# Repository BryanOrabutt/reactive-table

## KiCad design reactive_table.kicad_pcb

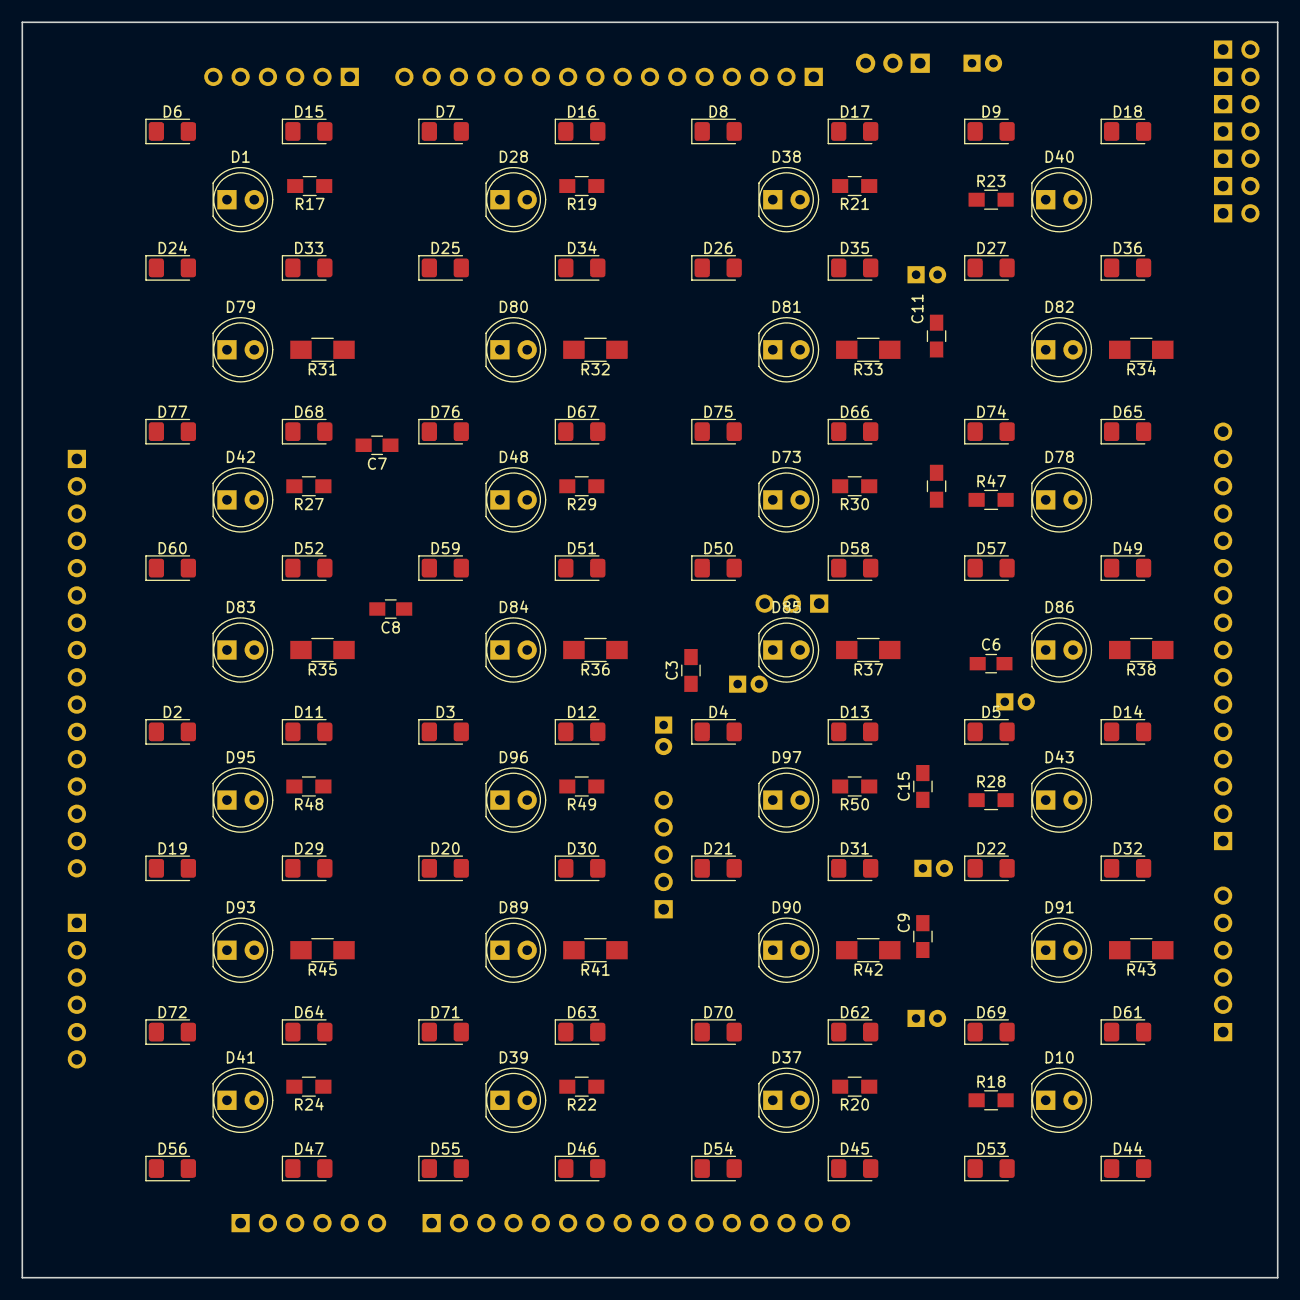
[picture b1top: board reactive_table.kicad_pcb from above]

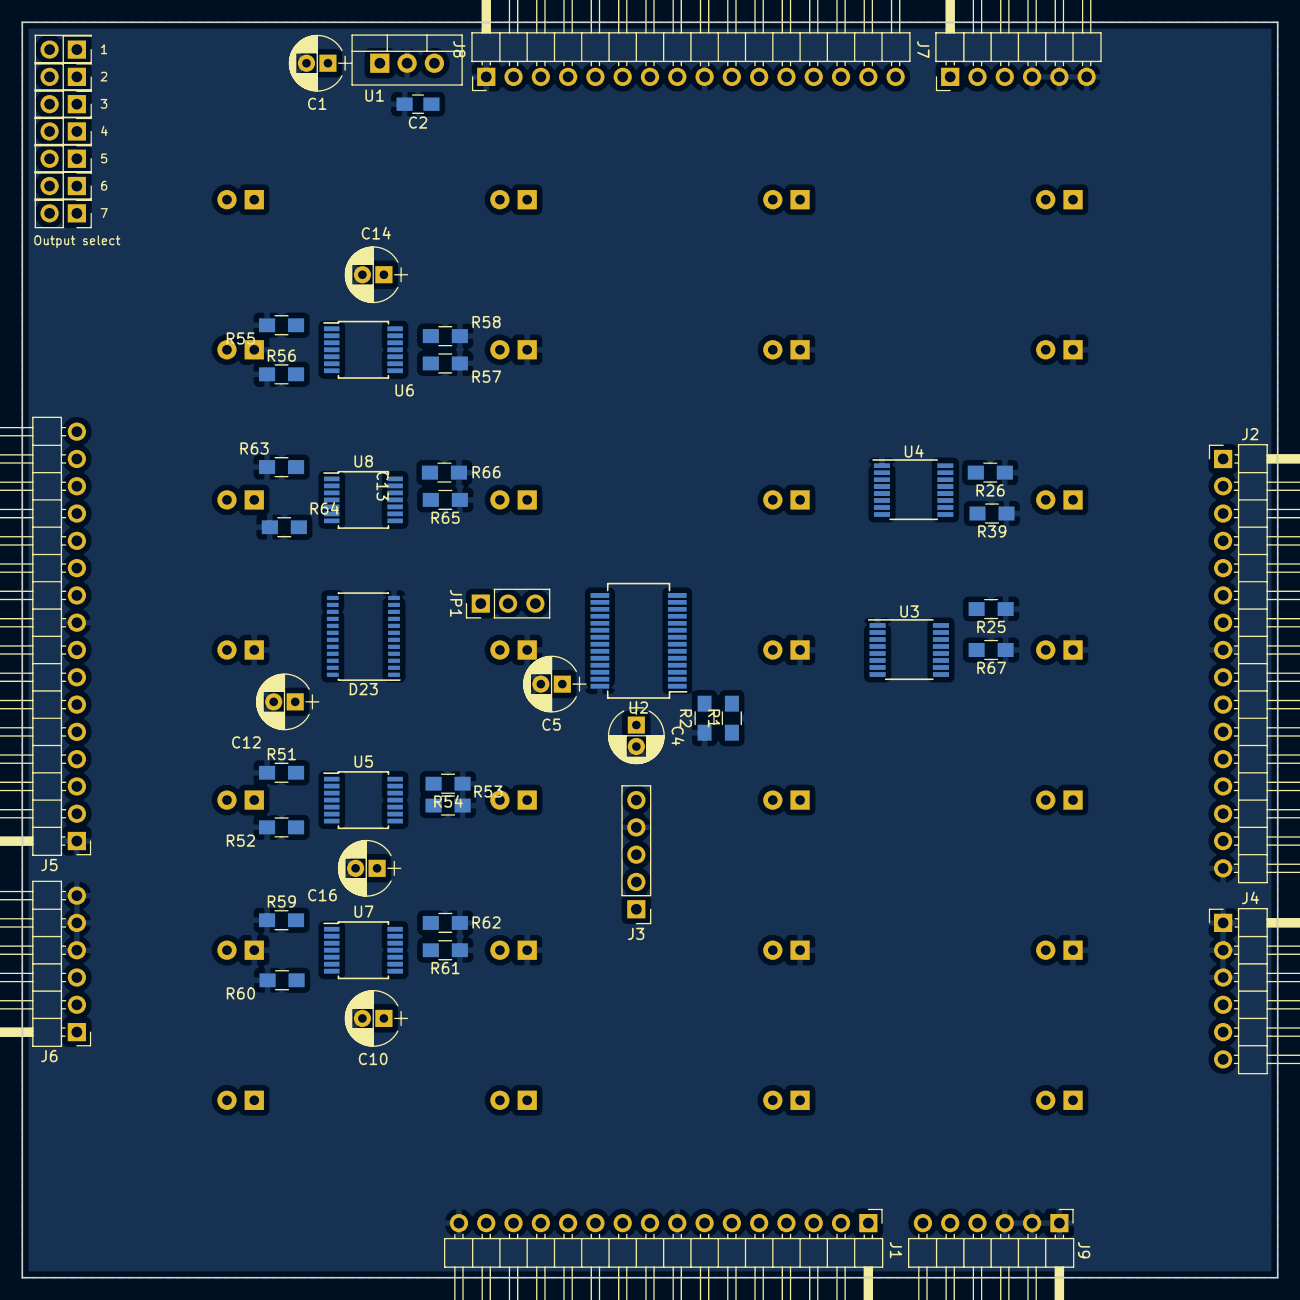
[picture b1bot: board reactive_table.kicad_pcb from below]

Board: 4 copper layers, 116.8 x 116.8 mm, 184 parts (56 on the bottom side), 137 nets, no tracks yet.

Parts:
C1, C4, C5, C10, C12, C14, C16: 1u; CP_Radial_D5.0mm_P2.00mm
C2, C3, C6, C7, C8, C9, C11, C13, C15: 100n; C_0805_HandSoldering
D1, D10, D28, D37, D38, D39, D40, D41, D42, D43, D48, D73, D78, D95, D96, D97: IR_RX; LED_D5.0mm
D2, D3, D4, D5, D6, D7, D8, D9, D11, D12, D13, D14, D15, D16, D17, D18, D19, D20, D21, D22, D24, D25, D26, D27, D29, D30, D31, D32, D33, D34, D35, D36, D44, D45, D46, D47, D49, D50, D51, D52, D53, D54, D55, D56, D57, D58, D59, D60, D61, D62, D63, D64, D65, D66, D67, D68, D69, D70, D71, D72, D74, D75, D76, D77: LED_Small; LED_1206_3216Metric_Pad1.42x1.75mm_HandSolder
D23: 74HC4067; TSSOP-24_4.4x7.8mm_Pitch0.65mm
D79, D80, D81, D82, D83, D84, D85, D86, D89, D90, D91, D93: IR_TX; LED_D5.0mm
J1: BOT; Pin_Header_Angled_1x16_Pitch2.54mm
J2: LEFT; Pin_Header_Angled_1x16_Pitch2.54mm
J3: PROGRAM; Pin_Header_Straight_1x05_Pitch2.54mm
J4: PWR_LEFT; Pin_Header_Angled_1x06_Pitch2.54mm
J5: RIGHT; Pin_Header_Angled_1x16_Pitch2.54mm
J6: PWR_RIGHT; Pin_Header_Angled_1x06_Pitch2.54mm
J7: PWR_BOT; Pin_Header_Angled_1x06_Pitch2.54mm
J8: TOP; Pin_Header_Angled_1x16_Pitch2.54mm
J9: PWR_TOP; Pin_Header_Angled_1x06_Pitch2.54mm
JP1: MASTER_SEL; Pin_Header_Straight_1x03_Pitch2.54mm
JP2, JP3, JP4, JP5, JP6, JP7, JP8: Jumper_NO_Small; Pin_Header_Straight_2x01_Pitch2.54mm
R1, R17, R18, R19, R20, R21, R22, R23, R24, R27, R28, R29, R30, R47, R48, R49, R50: 1K5; R_0805_HandSoldering
R2, R25, R26, R39, R67: 2K2; R_0805_HandSoldering
R31, R32, R33, R34, R35, R36, R37, R38, R41, R42, R43, R45: 300; R_1206_HandSoldering
R51, R52, R53, R54, R55, R56, R57, R58, R59, R60, R61, R62, R63, R64, R65, R66: 1M; R_0805_HandSoldering
U1: uA7805; TO-220-3_Vertical
U2: CY8C4124PVI-432; SSOP-28_5.3x10.2mm_Pitch0.65mm
U3, U4: STP08DP05; TSSOP-16_4.4x5mm_Pitch0.65mm
U5, U6, U7, U8: TLC274; TSSOP-14_4.4x5mm_Pitch0.65mm

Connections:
+5V: C2.1, C3.2, C4.1, C6.1, C7.2, C8.2, C9.1, C10.1, C11.1, C12.1, C13.1, C14.1, C15.1, C16.1, D1.1, D10.1, D23.24, D37.1, D39.1, D41.1, D43.1, J3.5, U1.3, U2.27, U3.16, U4.16, U5.4, U6.4, U7.4, U8.4
+12V: C1.1, D2.2, D3.2, D4.2, D5.2, D6.2, D7.2, D8.2, D9.2, D28.1, D38.1, D40.1, D42.1, D48.1, D69.2, D70.2, D71.2, D72.2, D73.1, D74.2, D75.2, D76.2, D77.2, D78.1, D95.1, D96.1, D97.1, J4.4, J4.5, J4.6, J6.1, J6.2, J6.3, J7.1, J7.2, J7.3, J9.4, J9.5, J9.6, R31.1, R32.1, R33.1, R34.1, R35.1, R36.1, R37.1, R38.1, R41.1, R42.1, R43.1, R45.1, U1.1
/BRD1: J1.7, J2.7, J5.10, J8.10, JP8.2, U2.4
/BRD2: J1.6, J2.6, J5.11, J8.11, JP7.2, U2.5
/BRD3: J1.5, J2.5, J5.12, J8.12, JP6.2, U2.6
/BRD4: J1.4, J2.4, J5.13, J8.13, JP5.2, U2.7
/BRD5: J1.3, J2.3, J5.14, J8.14, JP4.2, U2.8
/BRD6: J1.2, J2.2, J5.15, J8.15, JP3.2, U2.9
/BRD7: J1.1, J2.1, J5.16, J8.16, JP2.2, U2.10
/CLK: J1.14, J2.14, J5.3, J8.3, U2.20, U3.3, U4.3
/LE: J1.13, J2.13, J5.4, J8.4, U2.21, U3.4, U4.4
/LED Drivers & MUXs/DRIVER_SDI: JP1.2, U4.2
/LED Drivers & MUXs/DRIVER_SDO: J5.2, J8.2, U3.14
/LED Drivers & MUXs/IR0: D1.2, R17.2, R51.2, U5.3
/LED Drivers & MUXs/IR1: D28.2, R19.2, R52.2, U5.5
/LED Drivers & MUXs/IR2: D38.2, R21.2, R53.2, U5.10
/LED Drivers & MUXs/IR3: D40.2, R23.2, R54.2, U5.12
/LED Drivers & MUXs/IR4: D42.2, R27.2, R55.2, U6.3
/LED Drivers & MUXs/IR5: D48.2, R29.2, R56.2, U6.5
/LED Drivers & MUXs/IR6: D73.2, R30.2, R57.2, U6.10
/LED Drivers & MUXs/IR7: D78.2, R47.2, R58.2, U6.12
/LED Drivers & MUXs/IR8: D95.2, R48.2, R59.2, U7.3
/LED Drivers & MUXs/IR9: D96.2, R49.2, R60.2, U7.5
/LED Drivers & MUXs/IR10: D97.2, R50.2, R61.2, U7.10
/LED Drivers & MUXs/IR11: D43.2, R28.2, R62.2, U7.12
/LED Drivers & MUXs/IR12: D41.2, R24.2, R63.2, U8.3
/LED Drivers & MUXs/IR13: D39.2, R22.2, R64.2, U8.5
/LED Drivers & MUXs/IR14: D37.2, R20.2, R65.2, U8.10
/LED Drivers & MUXs/IR15: D10.2, R18.2, R66.2, U8.12
/LED Drivers & MUXs/sdo: U3.2, U4.14
/MUX0: D23.10, J1.9, J2.9, J5.8, J8.8, U2.18
/MUX1: D23.11, J1.10, J2.10, J5.7, J8.7, U2.17
/MUX2: D23.14, J1.11, J2.11, J5.6, J8.6, U2.16
/MUX3: D23.13, J1.12, J2.12, J5.5, J8.5, U2.15
/MUX_IN0: D23.9, U5.1, U5.2
/MUX_IN1: D23.8, U5.6, U5.7
/MUX_IN2: D23.7, U5.8, U5.9
/MUX_IN3: D23.6, U5.13, U5.14
/MUX_IN4: D23.5, U6.1, U6.2
/MUX_IN5: D23.4, U6.6, U6.7
/MUX_IN6: D23.3, U6.8, U6.9
/MUX_IN7: D23.2, U6.13, U6.14
/MUX_IN8: D23.23, U7.1, U7.2
/MUX_IN9: D23.22, U7.6, U7.7
/MUX_IN10: D23.21, U7.8, U7.9
/MUX_IN11: D23.20, U7.13, U7.14
/MUX_IN12: D23.19, U8.1, U8.2
/MUX_IN13: D23.18, U8.6, U8.7
/MUX_IN14: D23.17, U8.8, U8.9
/MUX_IN15: D23.16, U8.13, U8.14
/Microcontroller/BOARD0: JP2.1, JP3.1, JP4.1, JP5.1, JP6.1, JP7.1, JP8.1, R1.2, R2.1, U2.3
/Microcontroller/PSOC_SDO: JP1.1, U2.19
/Microcontroller/RST: J3.3, U2.25
/Microcontroller/SWDCLK: J3.2, U2.14
/Microcontroller/SWDIO: J3.1, U2.13
/SDI: J1.15, J2.15, JP1.3
GND: C1.2, C2.2, C3.1, C4.2, C5.2, C6.2, C7.1, C8.1, C9.2, C10.2, C11.2, C12.2, C13.2, C14.2, C15.2, C16.2, D23.12, D23.15, D79.1, D80.1, D81.1, D82.1, D83.1, D84.1, D85.1, D86.1, D89.1, D90.1, D91.1, D93.1, J1.8, J1.16, J2.8, J2.16, J3.4, J4.1, J4.2, J4.3, J5.1, J5.9, J6.4, J6.5, J6.6, J7.4, J7.5, J7.6, J8.1, J8.9, J9.1, J9.2, J9.3, R2.2, R17.1, R18.1, R19.1, R20.1, R21.1, R22.1, R23.1, R24.1, R25.1, R26.1, R27.1, R28.1, R29.1, R30.1, R39.1, R47.1, R48.1, R49.1, R50.1, R51.1, R52.1, R53.1, R54.1, R55.1, R56.1, R57.1, R58.1, R59.1, R60.1, R61.1, R62.1, R63.1, R64.1, R65.1, R66.1, R67.1, U1.2, U2.28, U3.1, U4.1, U5.11, U6.11, U7.11, U8.11
unnamed: C5.1, U2.26
unnamed: D11.1, D19.2
unnamed: D2.1, D11.2
unnamed: D12.1, D20.2
unnamed: D3.1, D12.2
unnamed: D13.1, D21.2
unnamed: D4.1, D13.2
unnamed: D14.1, D22.2
unnamed: D5.1, D14.2
unnamed: D15.1, D24.2
unnamed: D6.1, D15.2
unnamed: D16.1, D25.2
unnamed: D7.1, D16.2
unnamed: D17.1, D26.2
unnamed: D8.1, D17.2
unnamed: D18.1, D27.2
unnamed: D9.1, D18.2
unnamed: D19.1, D29.2
unnamed: D20.1, D30.2
unnamed: D21.1, D31.2
unnamed: D22.1, D32.2
unnamed: D23.1, R1.1
unnamed: D24.1, D33.2
unnamed: D25.1, D34.2
unnamed: D26.1, D35.2
unnamed: D27.1, D36.2
unnamed: D29.1, U3.5
unnamed: D30.1, U3.6
unnamed: D31.1, U3.7
unnamed: D32.1, U3.8
unnamed: D33.1, U4.5
unnamed: D34.1, U4.6
unnamed: D35.1, U4.7
unnamed: D36.1, U4.8
unnamed: D44.1, U3.12
unnamed: D44.2, D53.1
unnamed: D45.1, U3.11
unnamed: D45.2, D54.1
unnamed: D46.1, U3.10
unnamed: D46.2, D55.1
unnamed: D47.1, U3.9
unnamed: D47.2, D56.1
unnamed: D49.1, U4.12
unnamed: D49.2, D57.1
unnamed: D50.1, U4.11
unnamed: D50.2, D58.1
unnamed: D51.1, U4.10
unnamed: D51.2, D59.1
unnamed: D52.1, U4.9
unnamed: D52.2, D60.1
unnamed: D53.2, D61.1
unnamed: D54.2, D62.1
unnamed: D55.2, D63.1
unnamed: D56.2, D64.1
unnamed: D57.2, D65.1
unnamed: D58.2, D66.1
unnamed: D59.2, D67.1
unnamed: D60.2, D68.1
unnamed: D61.2, D69.1
unnamed: D62.2, D70.1
unnamed: D63.2, D71.1
unnamed: D64.2, D72.1
unnamed: D65.2, D74.1
unnamed: D66.2, D75.1
unnamed: D67.2, D76.1
unnamed: D68.2, D77.1
unnamed: D79.2, R31.2
unnamed: D80.2, R32.2
unnamed: D81.2, R33.2
unnamed: D82.2, R34.2
unnamed: D83.2, R35.2
unnamed: D84.2, R36.2
unnamed: D85.2, R37.2
unnamed: D86.2, R38.2
unnamed: D89.2, R41.2
unnamed: D90.2, R42.2
unnamed: D91.2, R43.2
unnamed: D93.2, R45.2
unnamed: R25.2, R67.2, U3.15
unnamed: R26.2, R39.2, U4.15

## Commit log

2019-05-28 Saving current progress to github
2019-05-28 Reworked schematic. Started board
2019-05-29 Update schematic sheets
2019-05-31 Add main power connector for master board
